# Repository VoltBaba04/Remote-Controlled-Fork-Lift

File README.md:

Remote-Controlled Forklift with Video Streaming

**Project Overview :** 
This project is a remote-controlled forklift system designed for industrial use, controlled using Arduino Nano with live video streaming via ESP32-CAM. The forklift is controlled remotely using two joysticks: one for 4WD vehicle movement and the other for forklift lift and angle control. The project uses NRF24L01 wireless modules for long-range communication between the transmitter and receiver. The ESP32-CAM module streams live video, allowing real-time monitoring of the forklift’s environment.

**System Architecture :** 
The system is divided into two main sections: the transmitter and the receiver.

**Transmitter:**
Arduino Nano: 
Processes inputs from joysticks.

**NRF24L01:**
Transmits the joystick control signals wirelessly.

**Two Joysticks:**
Joystick 1: Controls vehicle movement (forward, reverse, left, right).
Joystick 2: Controls forklift lifting and fork angle.

**Power Supply:**
Powered by USB or a regulated 5V power source.

**Receiver:**
Arduino Nano:
Receives commands and controls the motors.

**NRF24L01:**
Receives wireless signals from the transmitter.

**L298N Motor Drivers (2):**
One motor driver controls 4WD motors for vehicle movement.
The other motor driver controls the forklift lifting motor.

**ESP32-CAM:**
Streams live video for real-time monitoring of the forklift's surroundings.

**Li-ion Battery Packs:**
Two packs of 4 Li-ion cells (2500mAh each) connected in series and in parallel for sufficient voltage and current.

**Buck Converter:**
Steps down voltage from the battery pack for the Arduino and other components.

**Stop Switch:**
Prevents the forklift from over-extending when lifting.

**Hardware Components**

**Transmitter:**

**Arduino Nano:** 
Main controller for joystick input.

**NRF24L01 Module with External Antenna:** 
Wireless communication.

**Two Joysticks:**
For controlling the forklift.

**USB Power Supply:**
Or external 5V regulated supply.

**Receiver:**

**Arduino Nano:** 
Receives signals from the transmitter and controls the motors.

**NRF24L01 Module with External Antenna:**
Wireless communication.

**ESP32-CAM:**
Streams live video over Wi-Fi.

**L298N Motor Drivers (2):**
Motor Driver 1: 
Controls 4WD vehicle motors.

Motor Driver 2: 
Controls forklift lift motor.

Li-ion Batteries (8x 2500mAh):
Two packs connected in parallel and series (14.8V).

**Buck Converter:** 
To step down voltage for the Arduino Nano.

**Stop Switch:**
To control the upward motion of the forklift.

**Power Supply Setup**

Batteries: 
Two packs of 4 Li-ion batteries (2500mAh) in series, connected in parallel. Each battery provides 3.7V, so the total voltage is 14.8V.

Buck Converter:
Reduces the voltage from 14.8V to 5V for the Arduino Nano and NRF24L01.

**How to Set Up the Project**

**1. Transmitter Side Setup:**

**Hardware Connections:**

Connect two joysticks to the Arduino Nano:
Joystick 1 controls 4WD motors.
Joystick 2 controls forklift lifting and angle.
Connect the NRF24L01 module to the Arduino Nano.
Power the transmitter using USB or a regulated 5V power source.

**Upload Code:**
Write the code to read joystick inputs and send the 
data via NRF24L01.
Use the Arduino IDE to upload the transmitter code.

**2. Receiver Side Setup:**

**Hardware Connections:**

Connect the Arduino Nano to the NRF24L01 module.
Connect the ESP32-CAM module to stream live video over Wi-Fi.
Connect the L298N motor drivers to control the 4WD motors and forklift motor.
Connect the battery packs and buck converter to provide power to the receiver.
Add the stop switch to prevent the forklift from over-extending when lifting.

**Upload Code:**
Write the receiver code to handle motor control and video streaming.
Use the Arduino IDE to upload the receiver code.
Code and Software

**1. Transmitter Code:**
Reads inputs from the joysticks.
Sends control signals (for forklift movement and lifting) via NRF24L01.

**3. Receiver Code:**
Receives control signals via NRF24L01.
Controls the L298N motor drivers to move the forklift and operate the lift.
Streams live video using the ESP32-CAM module over Wi-Fi.

**5. Video Streaming Code (ESP32-CAM):**
The ESP32-CAM streams live video using its onboard camera module.
The video feed is accessible via a local IP address over the same Wi-Fi network.
Testing and Results

**1. Wireless Communication Range:**
The system maintains reliable communication within a range of approximately 200 meters using the NRF24L01 module with an external antenna.

**3. Video Streaming:**
The ESP32-CAM provides a live video feed with low latency, allowing the operator to view the forklift’s surroundings in real-time.

**5. Motor Control:**
The L298N motor drivers efficiently control the 4WD motors and the forklift lift motor, providing smooth operation.
Challenges and Solutions

**1. Power Management:**
Ensuring stable power supply for both the high-power motors and the low-power Arduino Nano and communication modules was a challenge.
The use of a buck converter to step down voltage ensured reliable operation without power fluctuations.

**3. Communication Range:**
The NRF24L01 module with an external antenna was chosen to ensure a reliable communication range of up to 200 meters, which is suitable for most industrial applications.
Future Improvements

**Autonomous Features:** Adding sensors for collision detection or autonomous movement.

**Improved Video Quality:** Upgrading to a higher resolution camera for clearer video feeds.

**Extended Range:** Using a more powerful communication module like LoRa for extended range operation.

**Battery Management System (BMS):** Integrating a BMS to protect the Li-ion batteries from overcharging and over-discharging.
Conclusion

This project successfully developed a remote-controlled forklift with live video streaming. It allows the operator to control the forklift’s movement and lifting mechanism remotely while viewing the surroundings via a live video stream. The system uses NRF24L01 for long-range wireless communication and ESP32-CAM for video streaming, making it a versatile and practical solution for industrial applications.

**References**
NRF24L01 Datasheet
ESP32-CAM Documentation
L298N Motor Driver Datasheet
Arduino Nano Pinout and Specifications

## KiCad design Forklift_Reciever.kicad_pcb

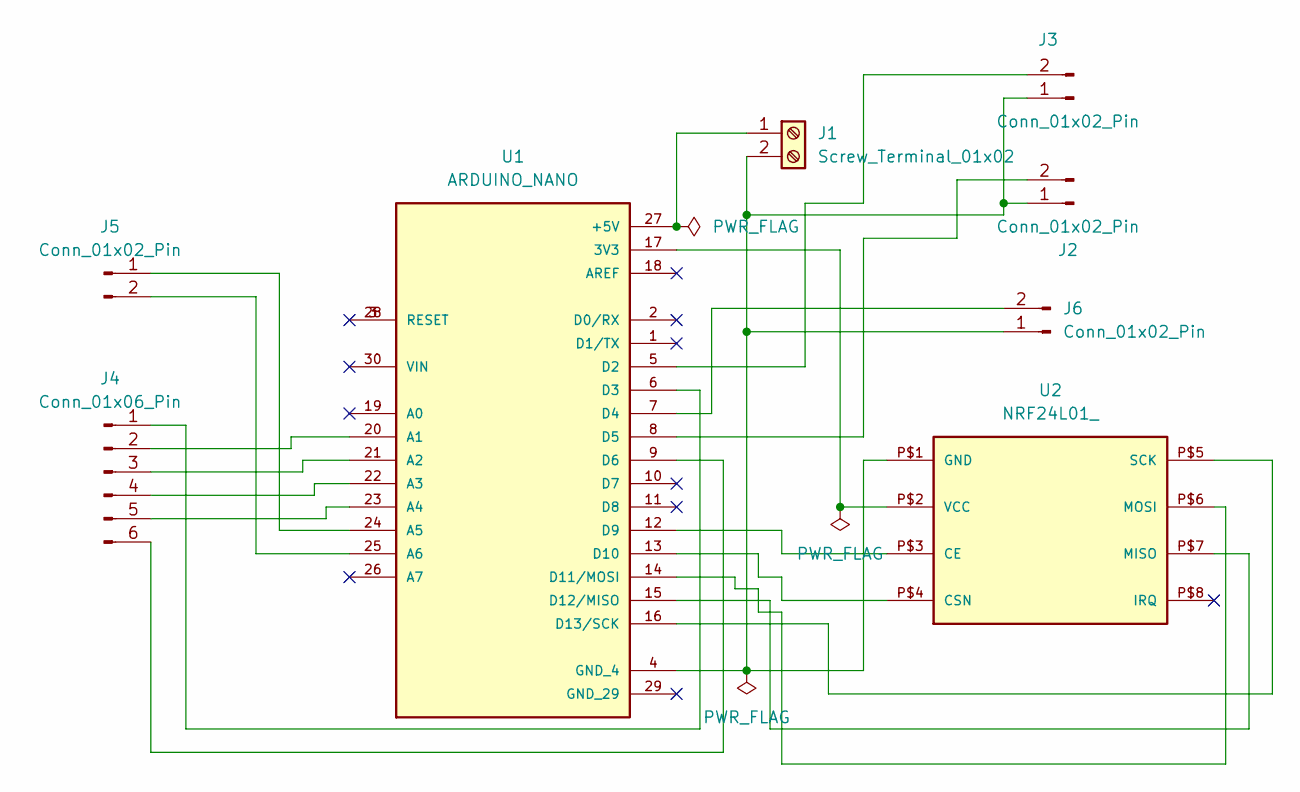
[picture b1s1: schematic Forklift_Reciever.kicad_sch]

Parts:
J1: Screw_Terminal_01x02; TerminalBlock_Phoenix_MKDS-1,5-2-5.08_1x02_P5.08mm_Horizont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
J2, J3, J5, J6: Conn_01x02_Pin; PinHeader_1x02_P2.54mm_Vertical
J4: Conn_01x06_Pin; PinHeader_1x06_P2.54mm_Vertical
U1: ARDUINO_NANO; MODULE_ARDUINO_NANO; PARTREV 30/06/2021
U2: NRF24L01_; NRF24L01-PCB-AERIAL

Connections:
unnamed: J1.1, U1.27 (+5V)
unnamed: J1.2, J2.1, J3.1, J6.1, U1.4 (GND_4), U2.P$1 (GND)
unnamed: J2.2, U1.8 (D5)
unnamed: J3.2, U1.5 (D2)
unnamed: J4.1, U1.6 (D3)
unnamed: J4.2, U1.20 (A1)
unnamed: J4.3, U1.21 (A2)
unnamed: J4.4, U1.22 (A3)
unnamed: J4.5, U1.23 (A4)
unnamed: J4.6, U1.9 (D6)
unnamed: J5.1, U1.24 (A5)
unnamed: J5.2, U1.25 (A6)
unnamed: J6.2, U1.7 (D4)
unnamed: U1.17 (3V3), U2.P$2 (VCC)
unnamed: U1.12 (D9), U2.P$3 (CE)
unnamed: U1.13 (D10), U2.P$4 (CSN)
unnamed: U1.14 (D11/MOSI), U2.P$6 (MOSI)
unnamed: U1.15 (D12/MISO), U2.P$7 (MISO)
unnamed: U1.16 (D13/SCK), U2.P$5 (SCK)

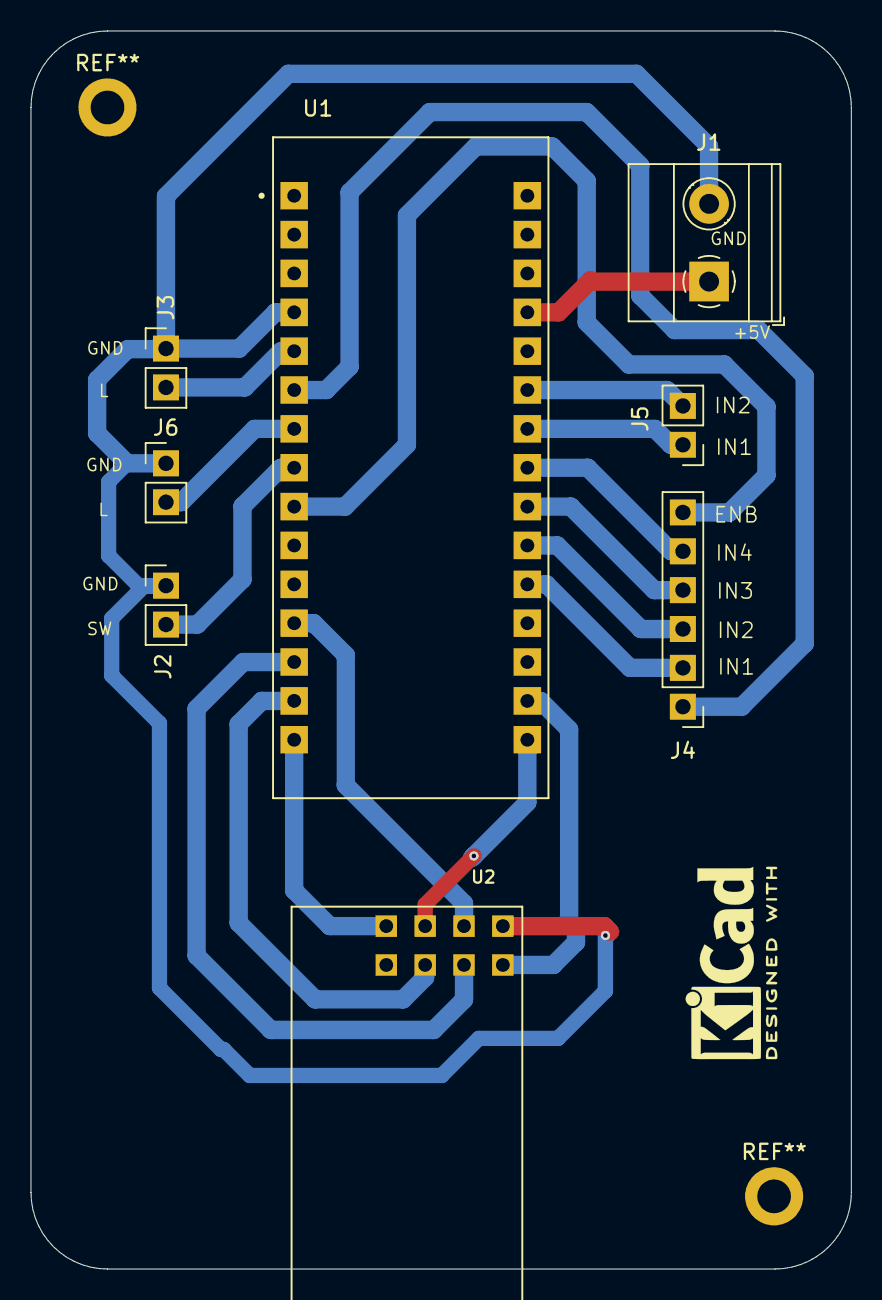
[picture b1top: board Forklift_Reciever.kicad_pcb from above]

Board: 2 copper layers, 53.6 x 80.9 mm, 8 parts (0 on the bottom side), 19 nets.
